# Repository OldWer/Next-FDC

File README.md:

# Next-FDC
A floppy drive controller for the ZX Spectrum Next (issues 1 and 2) based on the ZX Spectrum +3 FDC circuit. I have previously designed a version of this FDC that is compatible with the ZX Spectrum +2A and „turns it” into Spectrum +3, but it requires three signals (DRD, DRW, MTR) that are not present on the Next’s expansion bus (this applies to issues 1 and 2, issue 3 will have these signals on the bus). However, they can be fairly easily synthesized externally based on several data/address lines and that’s what I have done in this version.

<br/>The Next-FDC also works with regular ZX Spectrum +2A (and some clones, such as Sizif-512 and Harlequin 128), and I fully expect it to work with ZX Next issue 3 also (there just will be a little bit of redundancy, because in these cases the controller will create signals which are already being delivered by the computer itself).

Please note that in order to actually use the floppy drive with the Next you have to switch the computer into +3/+3e personality, change some settings and also issue several OUT commands (see below).
## How to make it?
The build is pretty self-explanatory. The gerbers are in the _gerbers_ directory; I have used recommended JLCPCB settings. The Bill of Materials is available in the _bom_ directory and all the parts are described on the PCB. The case model is available in the _STL_ directory. Actual FDC chips (uPD765 and SED9420) are still available pretty cheaply on Aliexpress (and I never got a fake one when ordering).

## How to use it?
In order to use the controller with the Next, you have to:
1. Switch the Next into +2A/+3 or +3e personality.
2. Press Space to go the configuration settings and disable DivmmcROM and DivmmcHW).
3. After reboot, go into +3 BASIC (or 48 BASIC).
4. Enter the following commands:
<br/>__OUT 9275, 136: OUT 9531, 223__
<br/>  _(Writing 223 to port 136 disables DACs that interfere with the FDC operation.)_
<br/>__OUT 9275, 138: OUT 9531, 8__
<br/>  _(Writing 8 to port 138 enables the port forwarding for port 1FFD to allow the I/O cycles to show up on the expansion bus.)_
<br/>__OUT 9275, 128: OUT 9531, 8__
<br/>  _(Writing 8 to port 128 enables the expansion bus.)_
5. Press Reset button.
6. Now go into BASIC again, enter the CAT command and see if it works!
I know that's pretty convoluted, but who knows, maybe Next developers can be talked into adding an appropriate option to the menu? ;-)

## Buttons
There are three buttons on the controller:
* The upper one (blue on the photo): switches disk side – you can e.g. format one side of a 3,5” floppy, then press this button and format/use the other side.
* The middle one (green): forces the READY signal when using IBM disk drives.
* The lower one (red): swaps drives A and B.

All these buttons can be used when the computer is switched on (obviously not in the middle of a disk operation).
## General remarks
* To use two IBM floppy drives, please use a floppy cable with the twist. To use a Gotek and an IBM drive, set the Gotek to DS1 and use a cable with the twist.
* Please note that to use HD floppies you have to cover the HD hole (e.g. with a piece of self-adhesive tape).
* Many thanks to Allen Albright and Tim Gilberts from the ZX Spectrum Next FB group, who had helped me with configuring the Next to support the FDC.
* If in doubt, contact me at oldwer@op.pl, I will be happy to help.

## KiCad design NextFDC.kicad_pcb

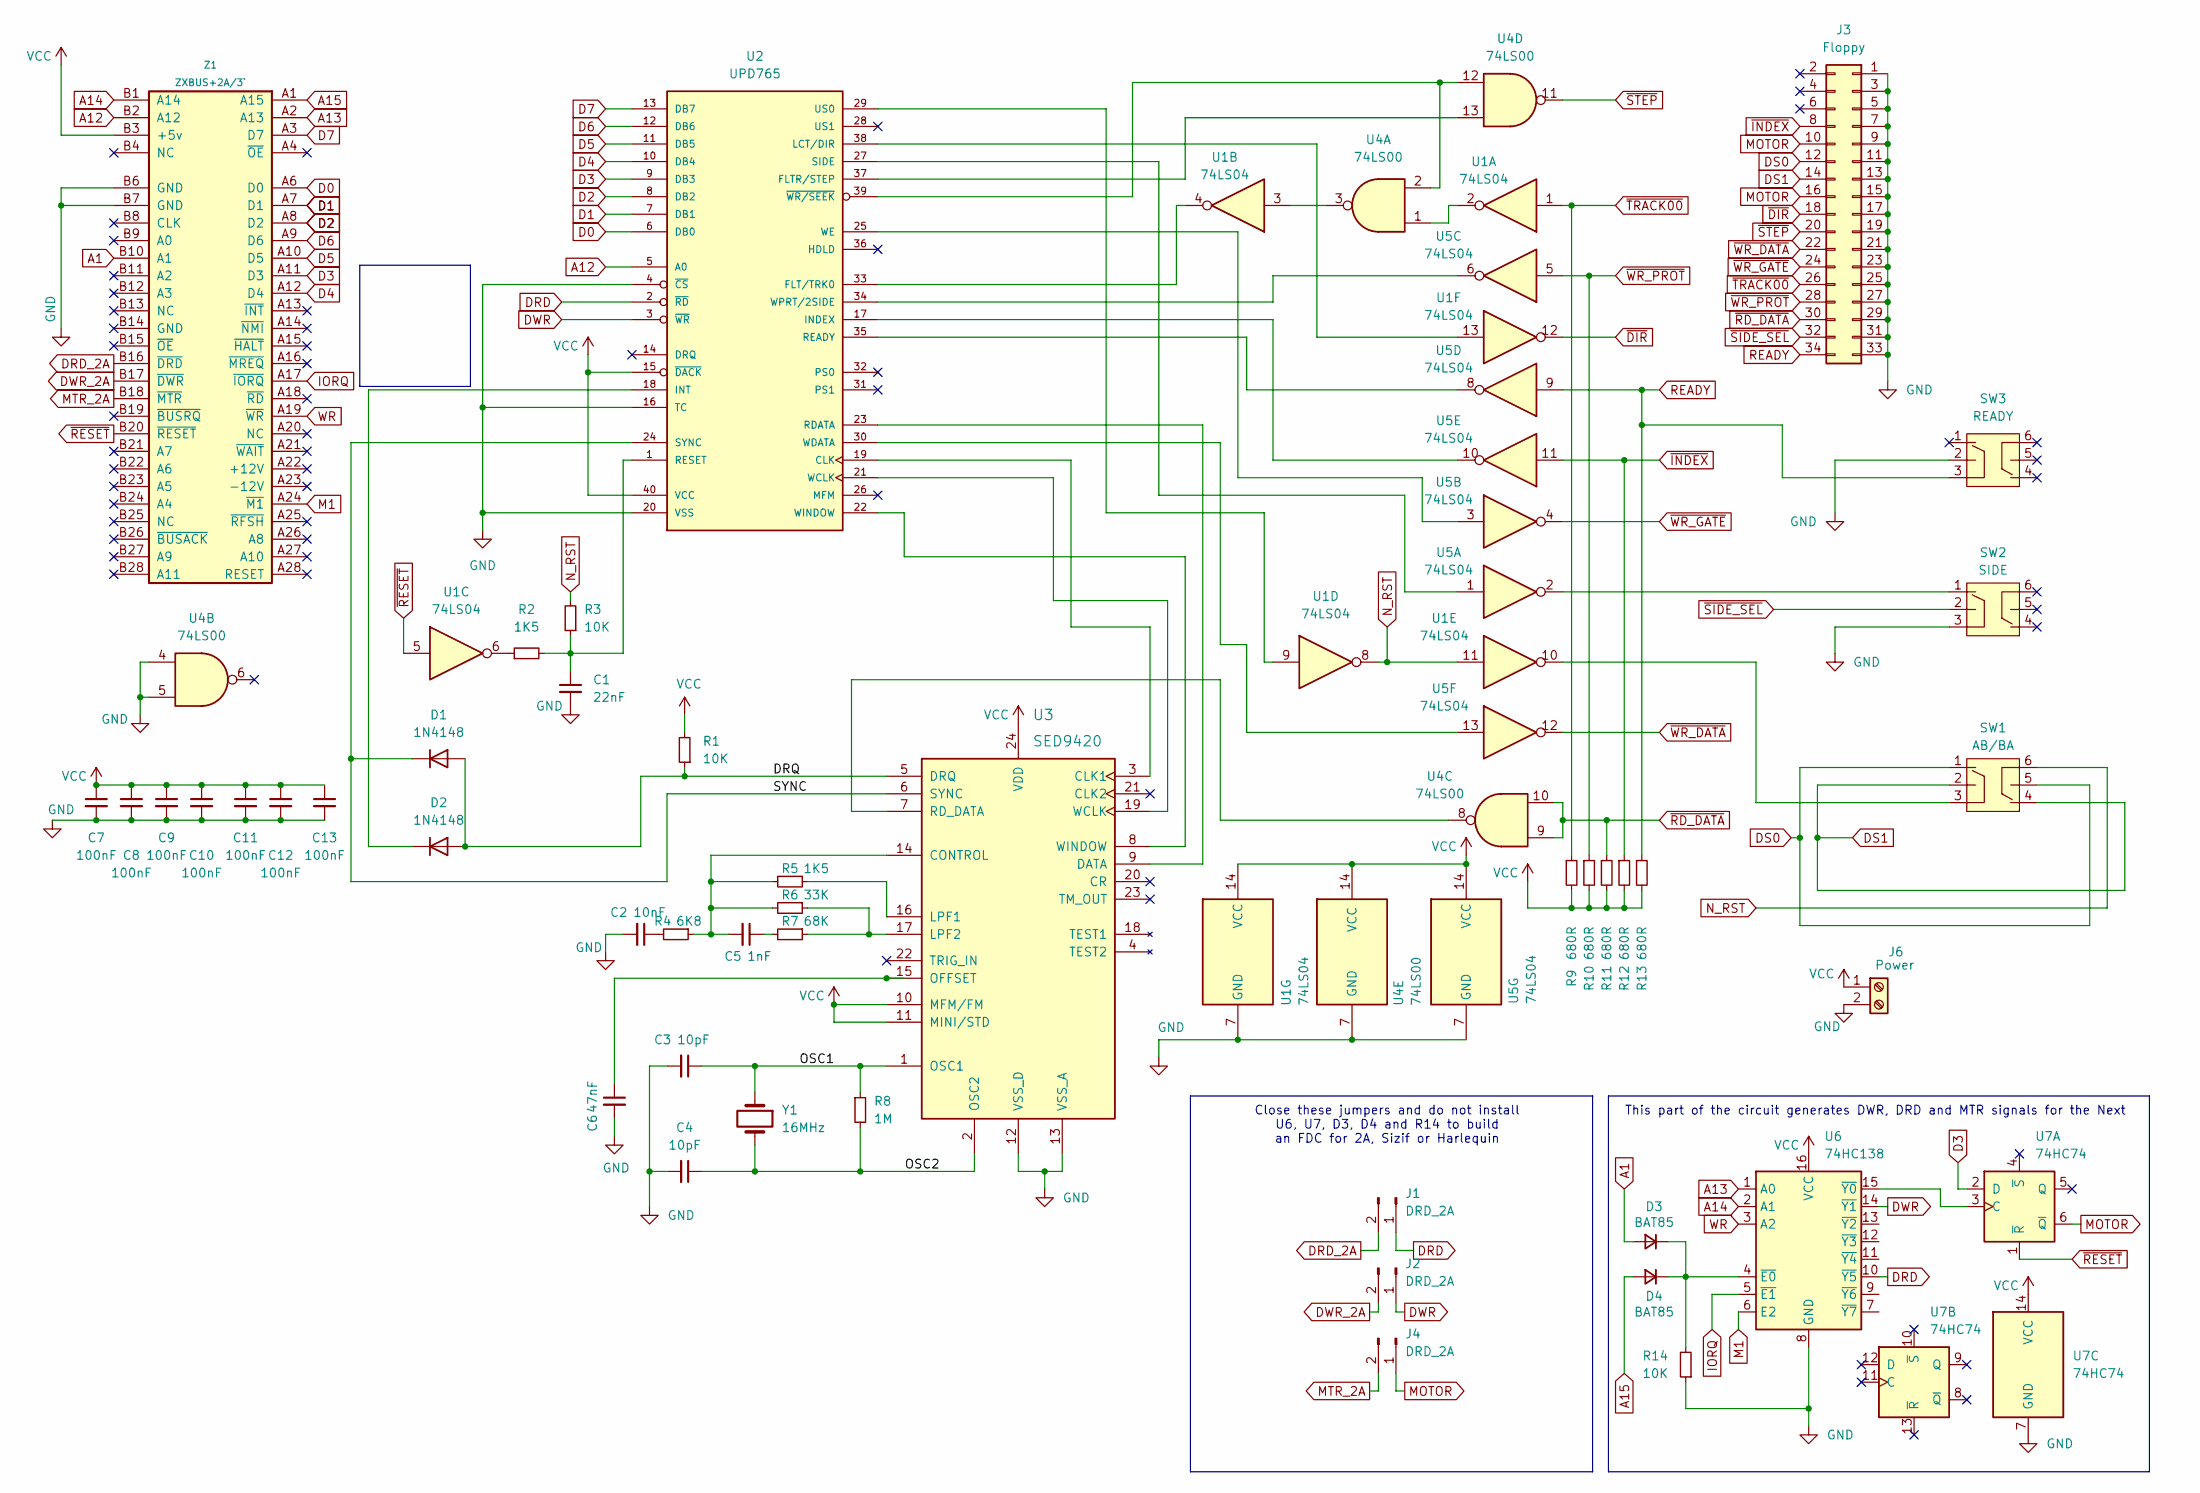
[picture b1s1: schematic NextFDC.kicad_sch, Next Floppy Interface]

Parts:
C1: 22nF; C_Disc_D4.3mm_W1.9mm_P5.00mm
C2: 10nF; C_Disc_D4.3mm_W1.9mm_P5.00mm
C3, C4: 10pF; C_Disc_D4.3mm_W1.9mm_P5.00mm
C5: 1nF; C_Disc_D4.3mm_W1.9mm_P5.00mm
C6: 47nF; C_Disc_D4.3mm_W1.9mm_P5.00mm
C7, C8, C9, C10, C11, C12, C13: 100nF; C_Disc_D4.3mm_W1.9mm_P5.00mm
D1, D2: 1N4148; D_DO-35_SOD27_P7.62mm_Horizontal
D3, D4: BAT85; D_DO-35_SOD27_P7.62mm_Horizontal
J1, J2, J4: DRD_2A; PinHeader_1x02_P2.54mm_Vertical
J3: Floppy; IDC-Header_2x17_P2.54mm_Vertical
J6: Power; TerminalBlock_bornier-2_P5.08mm
R1, R3, R14: 10K; R_Axial_DIN0207_L6.3mm_D2.5mm_P10.16mm_Horizontal
R2, R5: 1K5; R_Axial_DIN0207_L6.3mm_D2.5mm_P10.16mm_Horizontal
R4: 6K8; R_Axial_DIN0207_L6.3mm_D2.5mm_P10.16mm_Horizontal
R6: 33K; R_Axial_DIN0207_L6.3mm_D2.5mm_P10.16mm_Horizontal
R7: 68K; R_Axial_DIN0207_L6.3mm_D2.5mm_P10.16mm_Horizontal
R8: 1M; R_Axial_DIN0207_L6.3mm_D2.5mm_P10.16mm_Horizontal
R9, R10, R11, R12, R13: 680R; R_Axial_DIN0207_L6.3mm_D2.5mm_P10.16mm_Horizontal
SW1: AB/BA; SW_DPDT_XLX
SW2: SIDE; SW_DPDT_XLX
SW3: READY; SW_DPDT_XLX
U1, U5: 74LS04; DIP-14_W7.62mm_LongPads
U2: UPD765; DIP-40_W15.24mm_LongPads
U3: SED9420; DIP-24_W15.24mm_LongPads
U4: 74LS00; DIP-14_W7.62mm_LongPads
U6: 74HC138; DIP-16_W7.62mm_LongPads
U7: 74HC74; DIP-14_W7.62mm_LongPads
Y1: 16MHz; Crystal_HC49-U_Vertical
Z1: ZXBUS+2A/3`; ZX_CONN

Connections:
/DRQ: D1.2 (A), D2.2 (A), R1.1, U3.5 (DRQ)
/OSC1: C3.1, R8.1, U3.1 (OSC1), Y1.1
/OSC2: C4.1, R8.2, U3.2 (OSC2), Y1.2
/SYNC: D1.1 (K), U2.24 (SYNC), U3.6 (SYNC)
A1: D3.2 (A), Z1.B10 (A1)
A12: U2.5 (A0), Z1.B2 (A12)
A13: U6.1 (A0), Z1.A2 (A13)
A14: U6.2 (A1), Z1.B1 (A14)
A15: D4.2 (A), Z1.A1 (A15)
D0: U2.6 (DB0), Z1.A6 (D0)
D1: U2.7 (DB1), Z1.A7 (D1)
D2: U2.8 (DB2), Z1.A8 (D2)
D3: U2.9 (DB3), U7.2 (D), Z1.A11 (D3)
D4: U2.10 (DB4), Z1.A12 (D4)
D5: U2.11 (DB5), Z1.A10 (D5)
D6: U2.12 (DB6), Z1.A9 (D6)
D7: U2.13 (DB7), Z1.A3 (D7)
DRD: J1.1, U2.2 (~RD), U6.10 (~Y5)
DRD_2A: J1.2, Z1.B16 (~DRD)
DS0: J3.12, SW1.1, SW1.5
DS1: J3.14, SW1.2, SW1.4
DWR: J2.1, U2.3 (~WR), U6.14 (~Y1)
DWR_2A: J2.2, Z1.B17 (~DWR)
GND: C1.2, C2.2, C3.2, C4.2, C6.2, C7.2, C8.2, C9.2, C10.2, C11.2, C12.2, C13.2, J3.1, J3.3, J3.5, J3.7, J3.9, J3.11, J3.13, J3.15, J3.17, J3.19, J3.21, J3.23, J3.25, J3.27, J3.29, J3.31, J3.33, J6.2, R14.1, SW2.3, SW3.2, U1.7 (GND), U2.4 (~CS), U2.16 (TC), U2.20 (VSS), U3.12 (VSS_D), U3.13 (VSS_A), U4.4, U4.5, U4.7 (GND), U5.7 (GND), U6.8 (GND), U7.7 (GND), Z1.B6 (GND), Z1.B7 (GND)
IORQ: U6.5 (~E1), Z1.A17 (~IORQ)
M1: U6.6 (E2), Z1.A24 (~M1)
MOTOR: J3.10, J3.16, J4.1, U7.6 (~Q)
MTR_2A: J4.2, Z1.B18 (~MTR)
N_RST: R3.2, SW1.6, U1.8, U1.11
unnamed: C2.1, R4.2
unnamed: C5.1, R7.2
unnamed: D2.1 (K), U2.18 (INT)
unnamed: D3.1 (K), D4.1 (K), R14.2, U6.4 (~E0)
unnamed: R2.1, U1.6
unnamed: SW1.3, U1.10
unnamed: SW2.1, U5.2
unnamed: U1.2, U4.1
unnamed: U1.3, U4.3
unnamed: U2.19 (CLK), U3.3 (CLK1)
unnamed: U2.37 (FLTR/STEP), U4.13
unnamed: U1.4, U2.33 (FLT/TRK0)
unnamed: U2.17 (INDEX), U5.10
unnamed: U1.13, U2.38 (LCT/DIR)
unnamed: U2.23 (RDATA), U3.9 (DATA)
unnamed: U2.35 (READY), U5.8
unnamed: C1.1, R2.2, R3.1, U2.1 (RESET)
unnamed: U2.27 (SIDE), U5.1
unnamed: U1.9, U2.29 (US0)
unnamed: U2.21 (WCLK), U3.19 (WCLK)
unnamed: U2.30 (WDATA), U5.13
unnamed: U2.25 (WE), U5.3
unnamed: U2.22 (WINDOW), U3.8 (WINDOW)
unnamed: U2.34 (WPRT/2SIDE), U5.6
unnamed: U2.39 (~WR/SEEK), U4.2, U4.12
unnamed: C5.2, R4.1, R5.2, R6.2, U3.14 (CONTROL)
unnamed: R5.1, U3.16 (LPF1)
unnamed: R6.1, R7.1, U3.17 (LPF2)
unnamed: C6.1, U3.15 (OFFSET)
unnamed: U3.7 (RD_DATA), U4.8
unnamed: U6.15 (~Y0), U7.3 (C)
READY: J3.34, R13.1, SW3.3, U5.9
VCC: C7.1, C8.1, C9.1, C10.1, C11.1, C12.1, C13.1, J6.1, R1.2, R9.2, R10.2, R11.2, R12.2, R13.2, U1.14 (VCC), U2.15 (~DACK), U2.40 (VCC), U3.10 (MFM/FM), U3.11 (MINI/STD), U3.24 (VDD), U4.14 (VCC), U5.14 (VCC), U6.16 (VCC), U7.14 (VCC), Z1.B3 (+5v)
WR: U6.3 (A2), Z1.A19 (~WR)
~DIR: J3.18, U1.12
~INDEX: J3.8, R12.1, U5.11
~RD_DATA: J3.30, R11.1, U4.9, U4.10
~RESET: U1.5, U7.1 (~R), Z1.B20 (~RESET)
~SIDE_SEL: J3.32, SW2.2
~STEP: J3.20, U4.11
~TRACK00: J3.26, R9.1, U1.1
~WR_DATA: J3.22, U5.12
~WR_GATE: J3.24, U5.4
~WR_PROT: J3.28, R10.1, U5.5

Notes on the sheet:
This part of the circuit generates DWR, DRD and MTR signals for the Next
Close these jumpers and do not install U6, U7, D3, D4 and R14 to build an FDC for 2A, Sizif or Harlequin

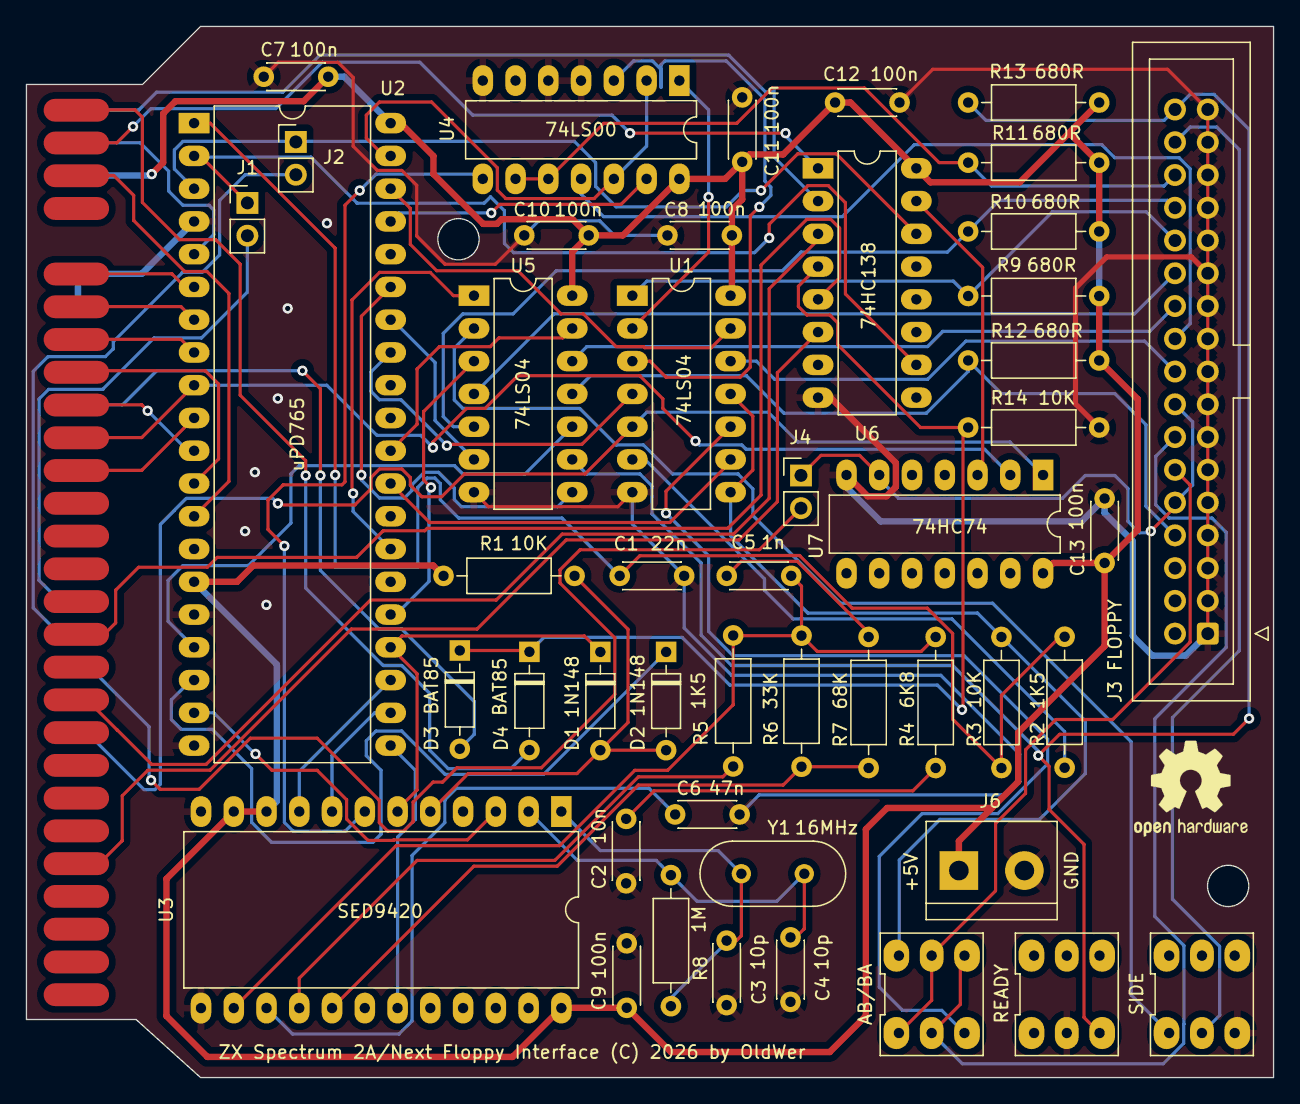
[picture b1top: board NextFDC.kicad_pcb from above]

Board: 2 copper layers, 96.7 x 81.5 mm, 48 parts (1 on the bottom side), 73 nets.

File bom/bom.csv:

"Reference","Value","Datasheet","Footprint","Qty","DNP"
"C1","22nF","~","Capacitor_THT:C_Disc_D4.3mm_W1.9mm_P5.00mm","1",""
"C2","10nF","~","Capacitor_THT:C_Disc_D4.3mm_W1.9mm_P5.00mm","1",""
"C3,C4","10pF","~","Capacitor_THT:C_Disc_D4.3mm_W1.9mm_P5.00mm","2",""
"C5","1nF","~","Capacitor_THT:C_Disc_D4.3mm_W1.9mm_P5.00mm","1",""
"C6","47nF","~","Capacitor_THT:C_Disc_D4.3mm_W1.9mm_P5.00mm","1",""
"C7,C8,C9,C10,C11,C12,C13","100nF","~","Capacitor_THT:C_Disc_D4.3mm_W1.9mm_P5.00mm","7",""
"D1,D2","1N4148","https://assets.nexperia.com/documents/data-sheet/1N4148_1N4448.pdf","Diode_THT:D_DO-35_SOD27_P7.62mm_Horizontal","2",""
"D3,D4","BAT85","~","Diode_THT:D_DO-35_SOD27_P7.62mm_Horizontal","2",""
"J1,J2,J4","DRD_2A","~","Connector_PinHeader_2.54mm:PinHeader_1x02_P2.54mm_Vertical","3",""
"J3","Floppy","~","Connector_IDC:IDC-Header_2x17_P2.54mm_Vertical","1",""
"J6","Power","~","TerminalBlock:TerminalBlock_bornier-2_P5.08mm","1",""
"R1,R3,R14","10K","~","Resistor_THT:R_Axial_DIN0207_L6.3mm_D2.5mm_P10.16mm_Horizontal","3",""
"R2,R5","1K5","~","Resistor_THT:R_Axial_DIN0207_L6.3mm_D2.5mm_P10.16mm_Horizontal","2",""
"R4","6K8","~","Resistor_THT:R_Axial_DIN0207_L6.3mm_D2.5mm_P10.16mm_Horizontal","1",""
"R6","33K","~","Resistor_THT:R_Axial_DIN0207_L6.3mm_D2.5mm_P10.16mm_Horizontal","1",""
"R7","68K","~","Resistor_THT:R_Axial_DIN0207_L6.3mm_D2.5mm_P10.16mm_Horizontal","1",""
"R8","1M","~","Resistor_THT:R_Axial_DIN0207_L6.3mm_D2.5mm_P10.16mm_Horizontal","1",""
"R9,R10,R11,R12,R13","680R","~","Resistor_THT:R_Axial_DIN0207_L6.3mm_D2.5mm_P10.16mm_Horizontal","5",""
"SW1","AB/BA","","SW_DPDT_XLX","1",""
"SW2","SIDE","","SW_DPDT_XLX","1",""
"SW3","READY","","SW_DPDT_XLX","1",""
"U1,U5","74LS04","http://www.ti.com/lit/gpn/sn74LS04","Package_DIP:DIP-14_W7.62mm_LongPads","2",""
"U2","UPD765","","Package_DIP:DIP-40_W15.24mm_LongPads","1",""
"U3","SED9420","","Package_DIP:DIP-24_W15.24mm_LongPads","1",""
"U4","74LS00","http://www.ti.com/lit/gpn/sn74ls00","Package_DIP:DIP-14_W7.62mm_LongPads","1",""
"U6","74HC138","http://www.ti.com/lit/ds/symlink/cd74hc238.pdf","Package_DIP:DIP-16_W7.62mm_LongPads","1",""
"U7","74HC74","74xx/74hc_hct74.pdf","Package_DIP:DIP-14_W7.62mm_LongPads","1",""
"Y1","16MHz","~","Crystal:Crystal_HC49-U_Vertical","1",""
"Z1","ZXBUS+2A/3`","","Common:ZX_CONN","1",""

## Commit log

2026-03-30 Enhance README with usage and build instructions
    Expanded the README to include detailed usage instructions, build information, and button functionalities for the floppy drive controller.
2026-03-30 Update README with images and usage instructions
    Added images
2026-03-30 Add acknowledgment for contributors in README
2026-03-30 Add gerber files information to README
2026-03-30 Update README to clarify button functionality
2026-03-30 Correct expansion bus enablement instruction
2026-03-30 Update README with additional usage instructions
2026-03-30 Fix redundancy in README description
    Corrected redundancy in description and improved clarity.
2026-03-30 Fix HTML entities and enhance README clarity
    Corrected HTML entities and improved clarity in the README.
2026-03-30 Fix typos and enhance README content
    Correct typos and improve clarity in README.
2026-04-14 Modify switch entries in bom.csv with size details
    Updated switch descriptions to include size information.

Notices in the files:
NextFDC.kicad_pcb:
ZX Spectrum 2A/Next Floppy Interface (C) 2026 by OldWer
